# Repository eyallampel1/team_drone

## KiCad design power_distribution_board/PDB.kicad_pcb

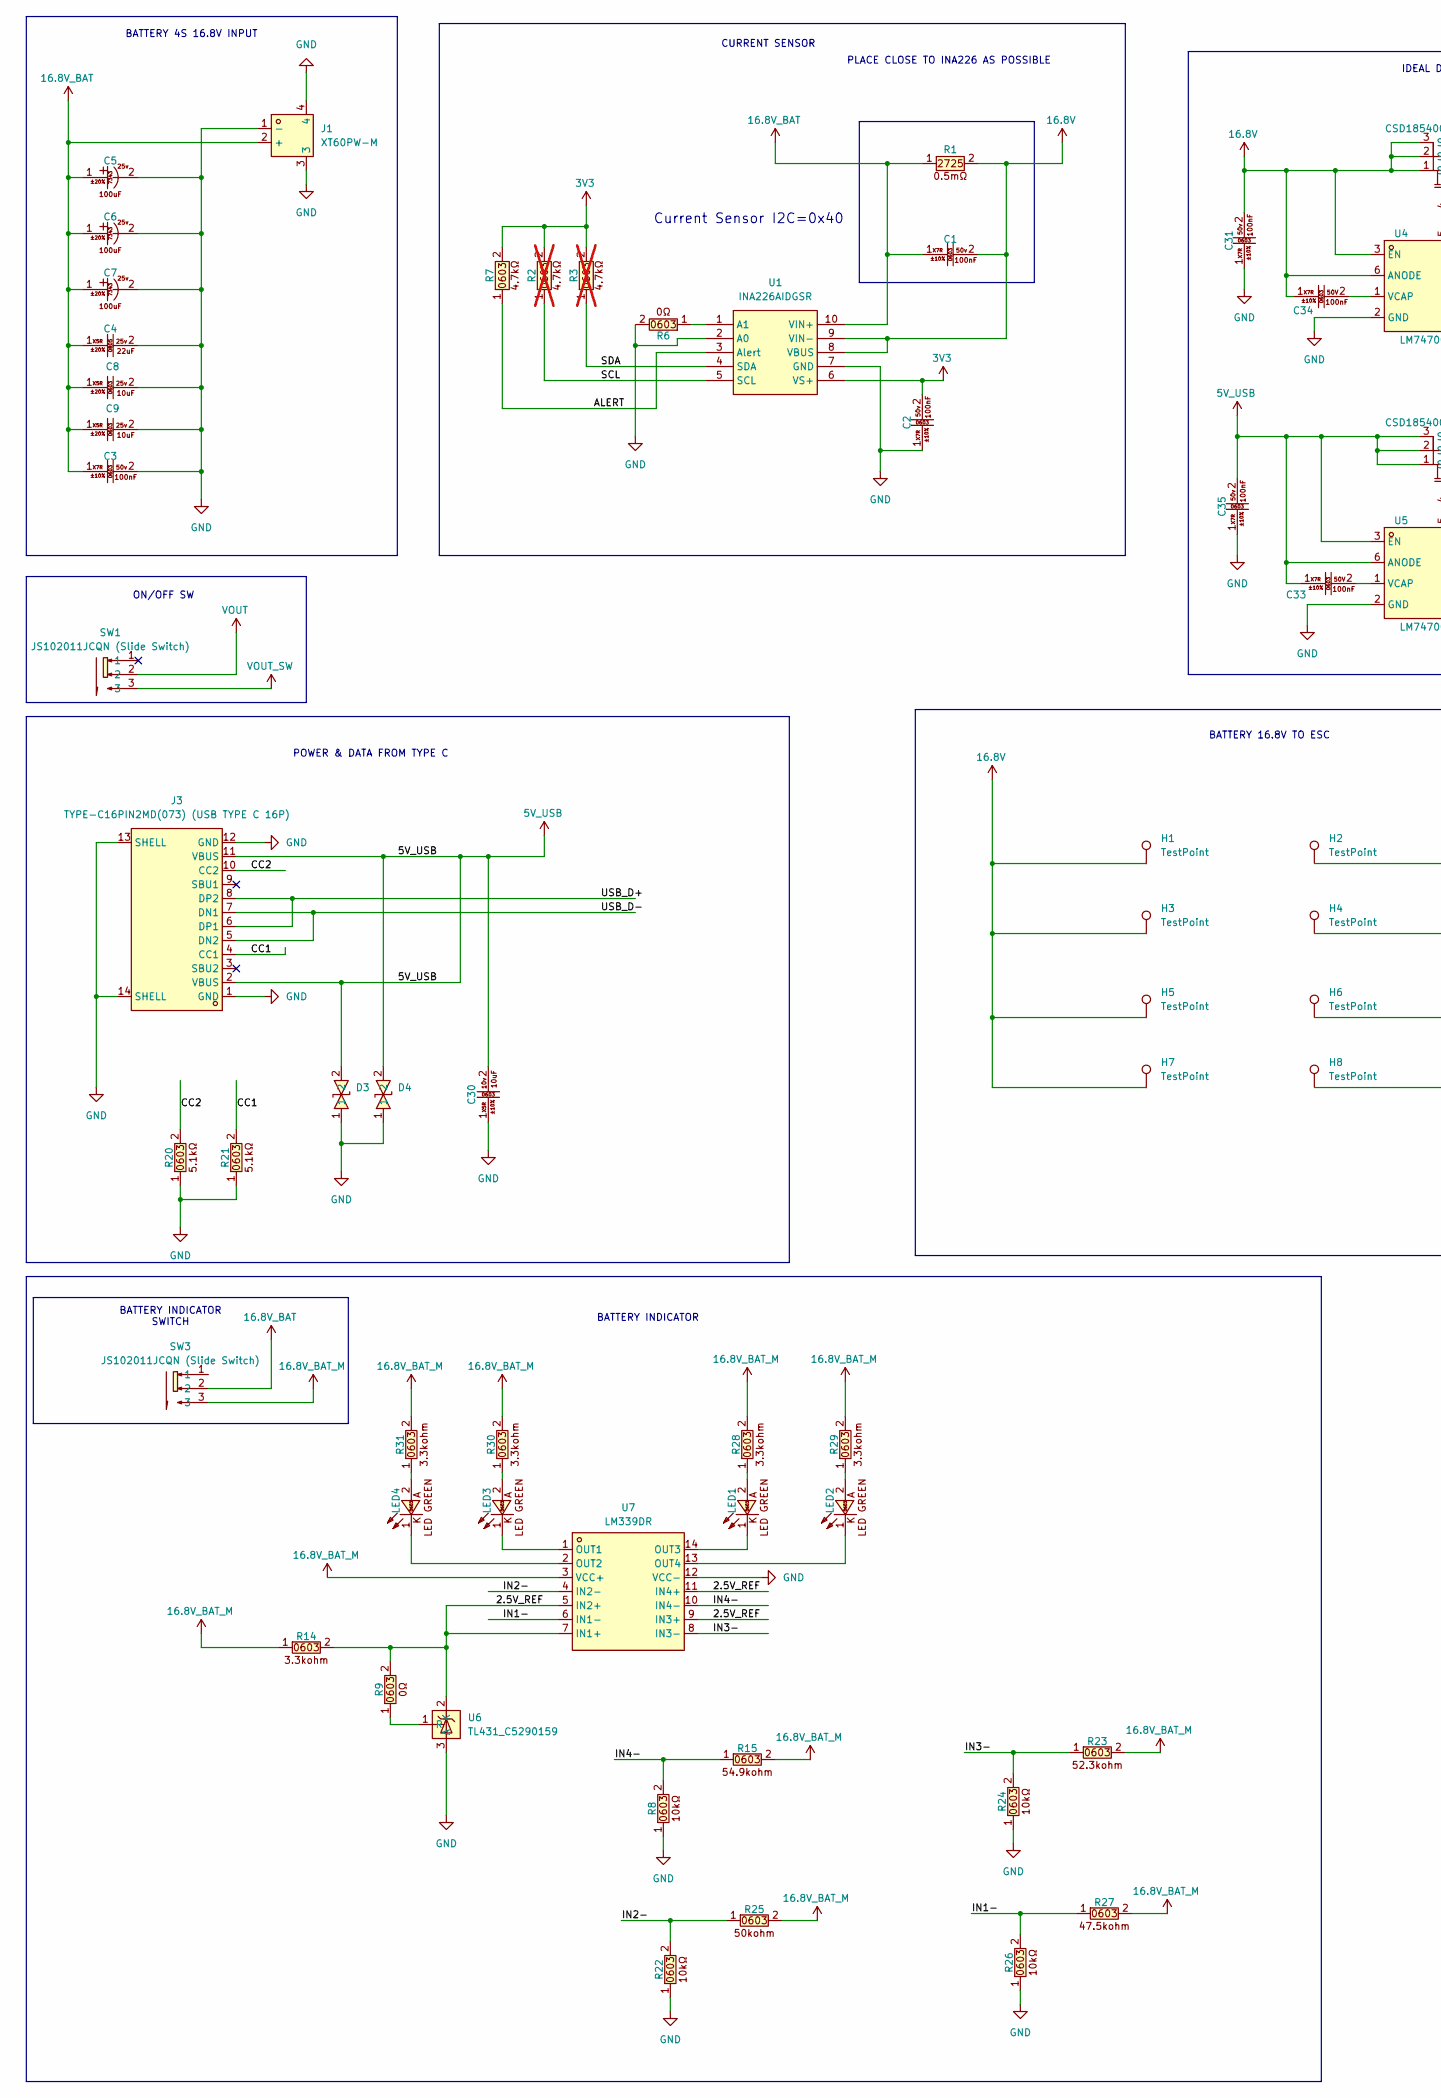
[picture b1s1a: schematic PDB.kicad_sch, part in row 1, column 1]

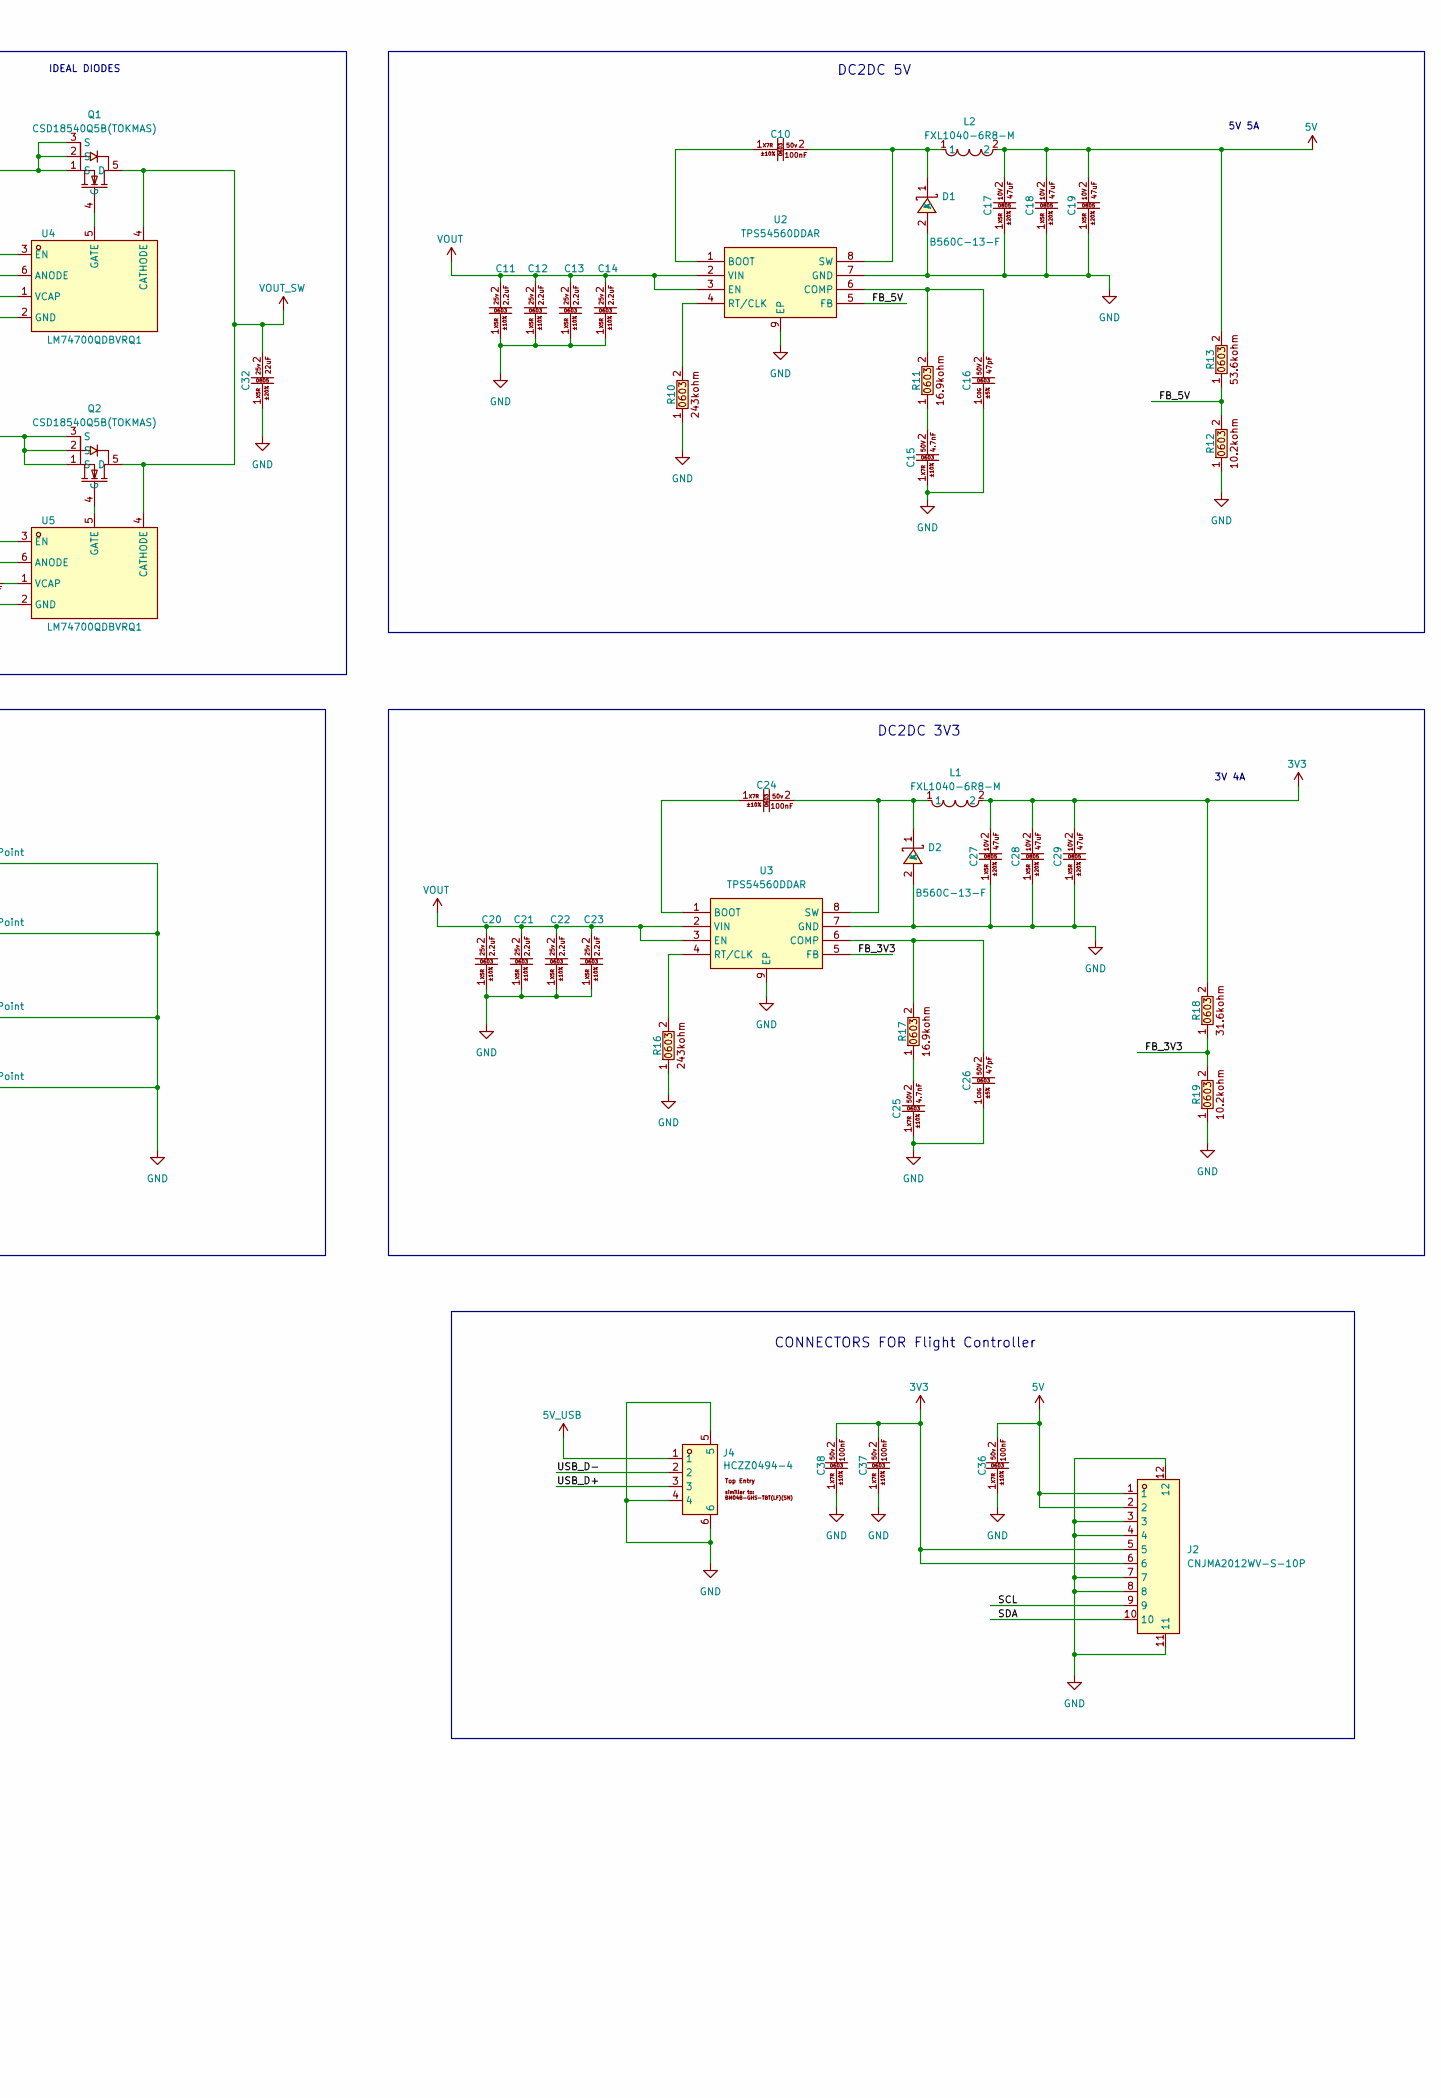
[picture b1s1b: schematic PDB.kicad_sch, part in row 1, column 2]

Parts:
C1, C2, C3, C10, C24, C31, C35, C36, C37, C38: CC0603KRX7R9BB104 (100nf , 0603 ,50v ,X7R); C0603; LCSC Part C14663
C4, C32: CL21A226MAYNNNE (22uf , 0805 ,25v ,X5R); C0805; LCSC Part C602037
C5, C6, C7: T521D107M025ATE040 (100uf , 7343 , 25v , tantalom); CAP-SMD_L7.3-W4.3_H2.8; LCSC Part C696814
C8, C9: CL10A106MA8NRNC (10uf , 0603 ,25v ,X5R); C0603; LCSC Part C96446
C11, C12, C13, C14, C20, C21, C22, C23: CL10A225KA8NNNC; C0603; LCSC Part C57895
C15, C25: CL10B472KB8NNNC (4.7nF , 0603 ,50V ,X7R); C0603; LCSC Part C1621
C16, C26: CL10C470JB8NNNC (47pF , 0603 ,50V ,C0G); C0603; LCSC Part C1671
C17, C18, C19, C27, C28, C29: GRM21BR61A476ME15L (47uF , 0805 ,10V ,X5R); C0805; LCSC Part C124129
C30: CL10A106KP8NNNC (10uf , 0603 ,10v,X5R); C0603; LCSC Part C19702
C33, C34: CC0603KRX7R9BB104 (100nF , 0603 ,50V ,X7R); C0603; LCSC Part C14663
D1, D2: B560C-13-F; SMC_L7.1-W6.2-LS8.1-RD; LCSC Part C85100
D3, D4: 603ESDA-05N (usb , esd , 0603); D0603-BI; LCSC Part C316054
H1, H2, H3, H4, H5, H6, H7, H8: TestPoint; TestPoint_THTPad_4.0x4.0mm_Drill2.0mm
J1: XT60PW-M; CONN-TH_XT60PW-M; LCSC Part C98732
J2: CNJMA2012WV-S-10P; CONN-SMD_10P-P2.00_CNJM_CNJMA2012WV-S-10P; LCSC Part C5151225
J3: TYPE-C16PIN2MD(073) (USB TYPE C 16P); USB-C-SMD_TYPE-C-6PIN-2MD-073; LCSC Part C2765186
J4: HCZZ0494-4; CONN-SMD_4P-P1.25_BM04B-GHS-TBT-LF-SN; LCSC Part C7433500
L1, L2: FXL1040-6R8-M; IND-SMD_L11.5-W10.0_FXL1040; LCSC Part C167231
LED1, LED2, LED3, LED4: 603Green509-620mcd (led green 0603); LED0603-RD; LCSC Part C12624
Q1, Q2: CSD18540Q5B(TOKMAS); TDSON-8_L5.9-W5.2-P1.27-BL; LCSC Part C19626234
R1: HOLR2725D-4W-0.5MR-1% ( 0.5mohm , 2725); R2725; LCSC Part C500744
R2, R3: FRC0603F4701TS (4.7kohm , 0603); R0603; LCSC Part C2907034; not fitted
R6, R9: 603WAF0000T5E (0ohm , 0603); R0603; LCSC Part C21189
R7: FRC0603F4701TS (4.7kohm , 0603); R0603; LCSC Part C2907034
R8, R22, R24, R26: 603WAF1002T5E (10kohm , 0603); R0603; LCSC Part C25804
R10, R16: 0603WAF2433T5E (243kohm , 0603); R0603; LCSC Part C23351
R11, R17: 0603WAF1692T5E (16.9kohm , 0603); R0603; LCSC Part C25954
R12, R19: 0603WAF1022T5E (10.2kohm , 0603); R0603; LCSC Part C22772
R13: 0603WAF5362T5E (53.6kohm , 0603); R0603; LCSC Part C23074
R14, R28, R29, R30, R31: 0603WAF3301T5E (3.3kohm , 0603); R0603; LCSC Part C22978
R15: 0603WAF5492T5E (54.9kohm , 0603); R0603; LCSC Part C23077
R18: 0603WAF3162T5E (31.6kohm , 0603); R0603; LCSC Part C25967
R20, R21: 603WAF5101T5E (5.1kohm , 0603); R0603; LCSC Part C23186
R23: 0603WAF5232T5E (52.3kohm , 0603); R0603; LCSC Part C23198
R25: RT0603BRD0750KL (50kohm , 0603); R0603; LCSC Part C861451
R27: 0603WAF4752T5E (47.5kohm , 0603); R0603; LCSC Part C23061
SW1, SW3: JS102011JCQN (Slide Switch); SW-SMD_JS102011JCQN; LCSC Part C221659
U1: INA226AIDGSR; MSOP-10_L3.0-W3.0-P0.50-LS5.0-BL; LCSC Part C49851
U2, U3: TPS54560DDAR; SOIC-8_L5.0-W4.0-P1.27-LS6.0-BL-EP2.0; LCSC Part C31966
U4, U5: LM74700QDBVRQ1; SOT-23-6_L2.9-W1.6-P0.95-LS2.8-BL; LCSC Part C2941042
U6: TL431_C5290159; SOT-23-3_L2.9-W1.4-P1.90-LS2.6-BR; LCSC Part C5290159
U7: LM339DR; SOIC-14_L8.7-W3.9-P1.27-LS6.0-BL; LCSC Part C7948

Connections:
3V3: C2.2, C27.2, C28.2, C29.2, C37.2, C38.2, J2.5, J2.6, L1.2, R2.2, R3.2, R7.2, R18.2, U1.6 (VS+)
5V: C17.2, C18.2, C19.2, C36.2, J2.1, J2.2, L2.2, R13.2
5V_USB: C30.2, C33.1, C35.2, D3.2, D4.2, J3.2 (VBUS), J3.11 (VBUS), J4.1, Q2.1 (S), Q2.2 (S), Q2.3 (S), U5.3 (EN), U5.6 (ANODE)
16.8V: C1.2, C31.2, C34.1, H1.1, H3.1, H5.1, H7.1, Q1.1 (S), Q1.2 (S), Q1.3 (S), R1.2, U1.8 (VBUS), U1.9 (VIN-), U4.3 (EN), U4.6 (ANODE)
16.8V_BAT: C1.1, C3.1, C4.1, C5.1, C6.1, C7.1, C8.1, C9.1, J1.2 (+), R1.1, SW3.2, U1.10 (VIN+)
16.8V_BAT_M: R14.1, R15.2, R23.2, R25.2, R27.2, R28.2, R29.2, R30.2, R31.2, SW3.3, U7.3 (VCC+)
/2.5V_REF: R9.2, R14.2, U6.2 (K), U7.5 (IN2+), U7.7 (IN1+), U7.9 (IN3+), U7.11 (IN4+)
/ALERT: R7.1, U1.3 (Alert)
/CC1: J3.4 (CC1), R21.2
/CC2: J3.10 (CC2), R20.2
/FB_3V3: R18.1, R19.2, U3.5 (FB)
/FB_5V: R12.2, R13.1, U2.5 (FB)
/IN1-: R26.2, R27.1, U7.6 (IN1-)
/IN2-: R22.2, R25.1, U7.4 (IN2-)
/IN3-: R23.1, R24.2, U7.8 (IN3-)
/IN4-: R8.2, R15.1, U7.10 (IN4-)
/SCL: J2.9, R2.1, U1.5 (SCL)
/SDA: J2.10, R3.1, U1.4 (SDA)
/USB_D+: J3.6 (DP1), J3.8 (DP2), J4.3
/USB_D-: J3.5 (DN2), J3.7 (DN1), J4.2
GND: C2.1, C3.2, C4.2, C5.2, C6.2, C7.2, C8.2, C9.2, C11.1, C12.1, C13.1, C14.1, C15.1, C16.1, C17.1, C18.1, C19.1, C20.1, C21.1, C22.1, C23.1, C25.1, C26.1, C27.1, C28.1, C29.1, C30.1, C31.1, C32.1, C35.1, C36.1, C37.1, C38.1, D1.2 (A), D2.2 (A), D3.1, D4.1, H2.1, H4.1, H6.1, H8.1, J1.1 (-), J1.3, J1.4, J2.3, J2.4, J2.7, J2.8, J2.11, J2.12, J3.1 (GND), J3.12 (GND), J3.13 (SHELL), J3.14 (SHELL), J4.4, J4.5, J4.6, R6.2, R8.1, R10.1, R12.1, R16.1, R19.1, R20.1, R21.1, R22.1, R24.1, R26.1, U1.2 (A0), U1.7 (GND), U2.7 (GND), U2.9 (EP), U3.7 (GND), U3.9 (EP), U4.2 (GND), U5.2 (GND), U6.3 (A), U7.12 (VCC-)
unnamed: C15.2, R11.1
unnamed: C25.2, R17.1
unnamed: C10.2, D1.1 (K), L2.1, U2.8 (SW)
unnamed: C24.2, D2.1 (K), L1.1, U3.8 (SW)
unnamed: LED1.2, R28.1
unnamed: LED2.2, R29.1
unnamed: LED3.2, R30.1
unnamed: LED4.2, R31.1
unnamed: Q1.4 (G), U4.5 (GATE)
unnamed: Q2.4 (G), U5.5 (GATE)
unnamed: R6.1, U1.1 (A1)
unnamed: C10.1, U2.1 (BOOT)
unnamed: C16.2, R11.2, U2.6 (COMP)
unnamed: R10.2, U2.4 (RT/CLK)
unnamed: C24.1, U3.1 (BOOT)
unnamed: C26.2, R17.2, U3.6 (COMP)
unnamed: R16.2, U3.4 (RT/CLK)
unnamed: C34.2, U4.1 (VCAP)
unnamed: C33.2, U5.1 (VCAP)
unnamed: R9.1, U6.1 (R)
unnamed: LED3.1, U7.1 (OUT1)
unnamed: LED4.1, U7.2 (OUT2)
unnamed: LED1.1, U7.14 (OUT3)
unnamed: LED2.1, U7.13 (OUT4)
VOUT: C11.2, C12.2, C13.2, C14.2, C20.2, C21.2, C22.2, C23.2, SW1.2, U2.2 (VIN), U2.3 (EN), U3.2 (VIN), U3.3 (EN)
VOUT_SW: C32.2, Q1.5 (D), Q2.5 (D), SW1.3, U4.4 (CATHODE), U5.4 (CATHODE)

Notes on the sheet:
Current Sensor I2C=0x40
CONNECTORS FOR Flight Controller
DC2DC 5V
PLACE CLOSE TO INA226 AS POSSIBLE
POWER & DATA FROM TYPE C
5V 5A
BATTERY 4S 16.8V INPUT
BATTERY INDICATOR
DC2DC 3V3
CURRENT SENSOR
BATTERY INDICATOR SWITCH
IDEAL DIODES
ON/OFF SW
BATTERY 16.8V TO ESC
3V 4A

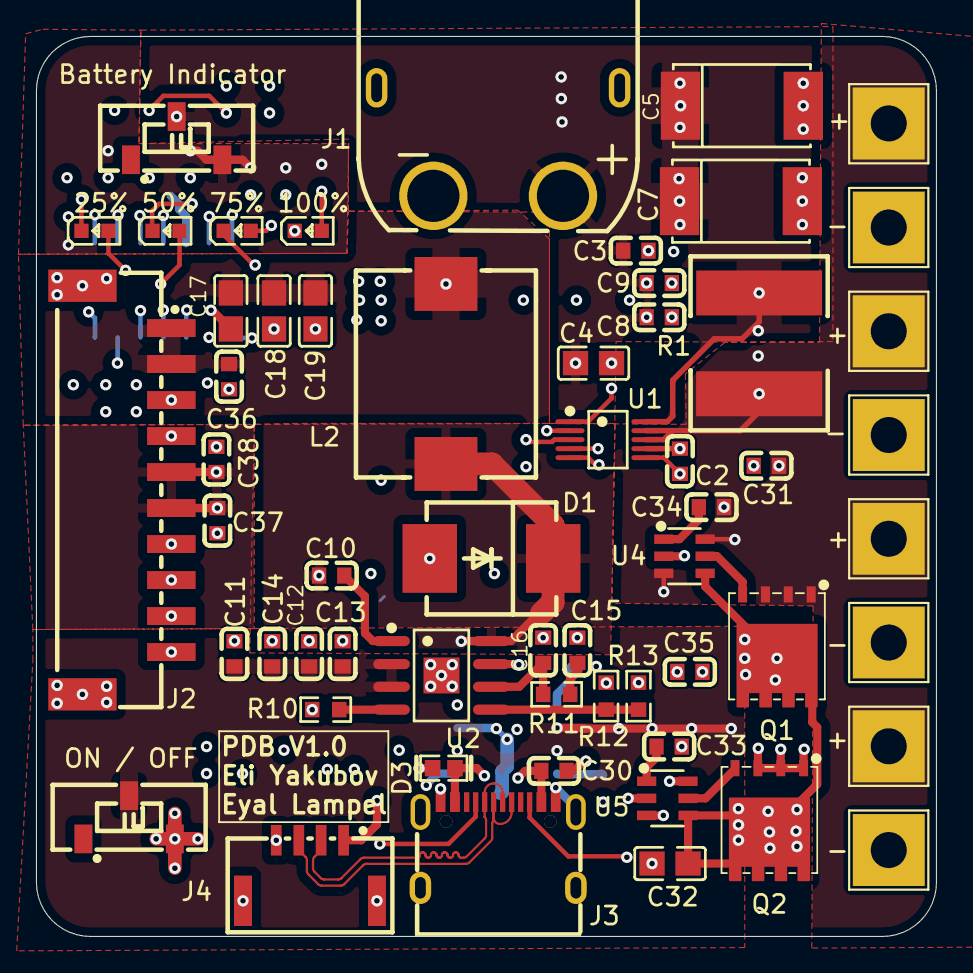
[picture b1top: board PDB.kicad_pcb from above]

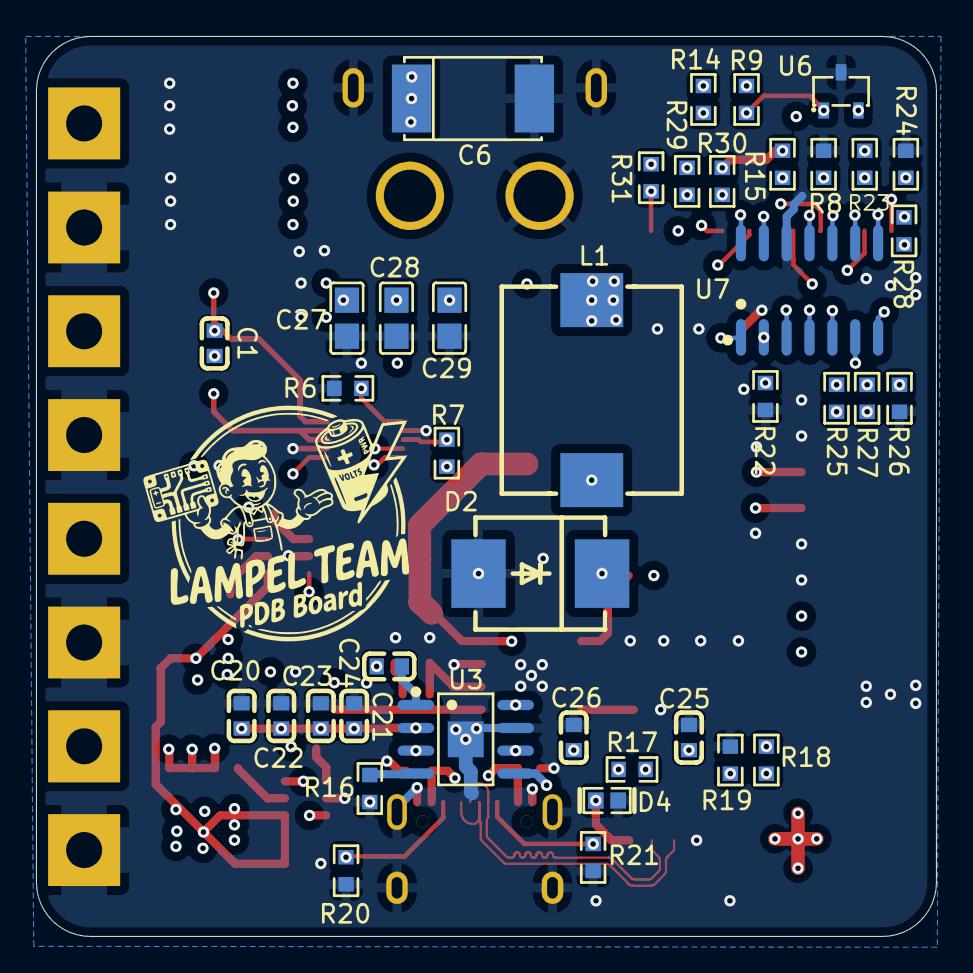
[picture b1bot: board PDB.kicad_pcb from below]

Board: 6 copper layers, 50.0 x 50.0 mm, 98 parts (40 on the bottom side), 47 nets.

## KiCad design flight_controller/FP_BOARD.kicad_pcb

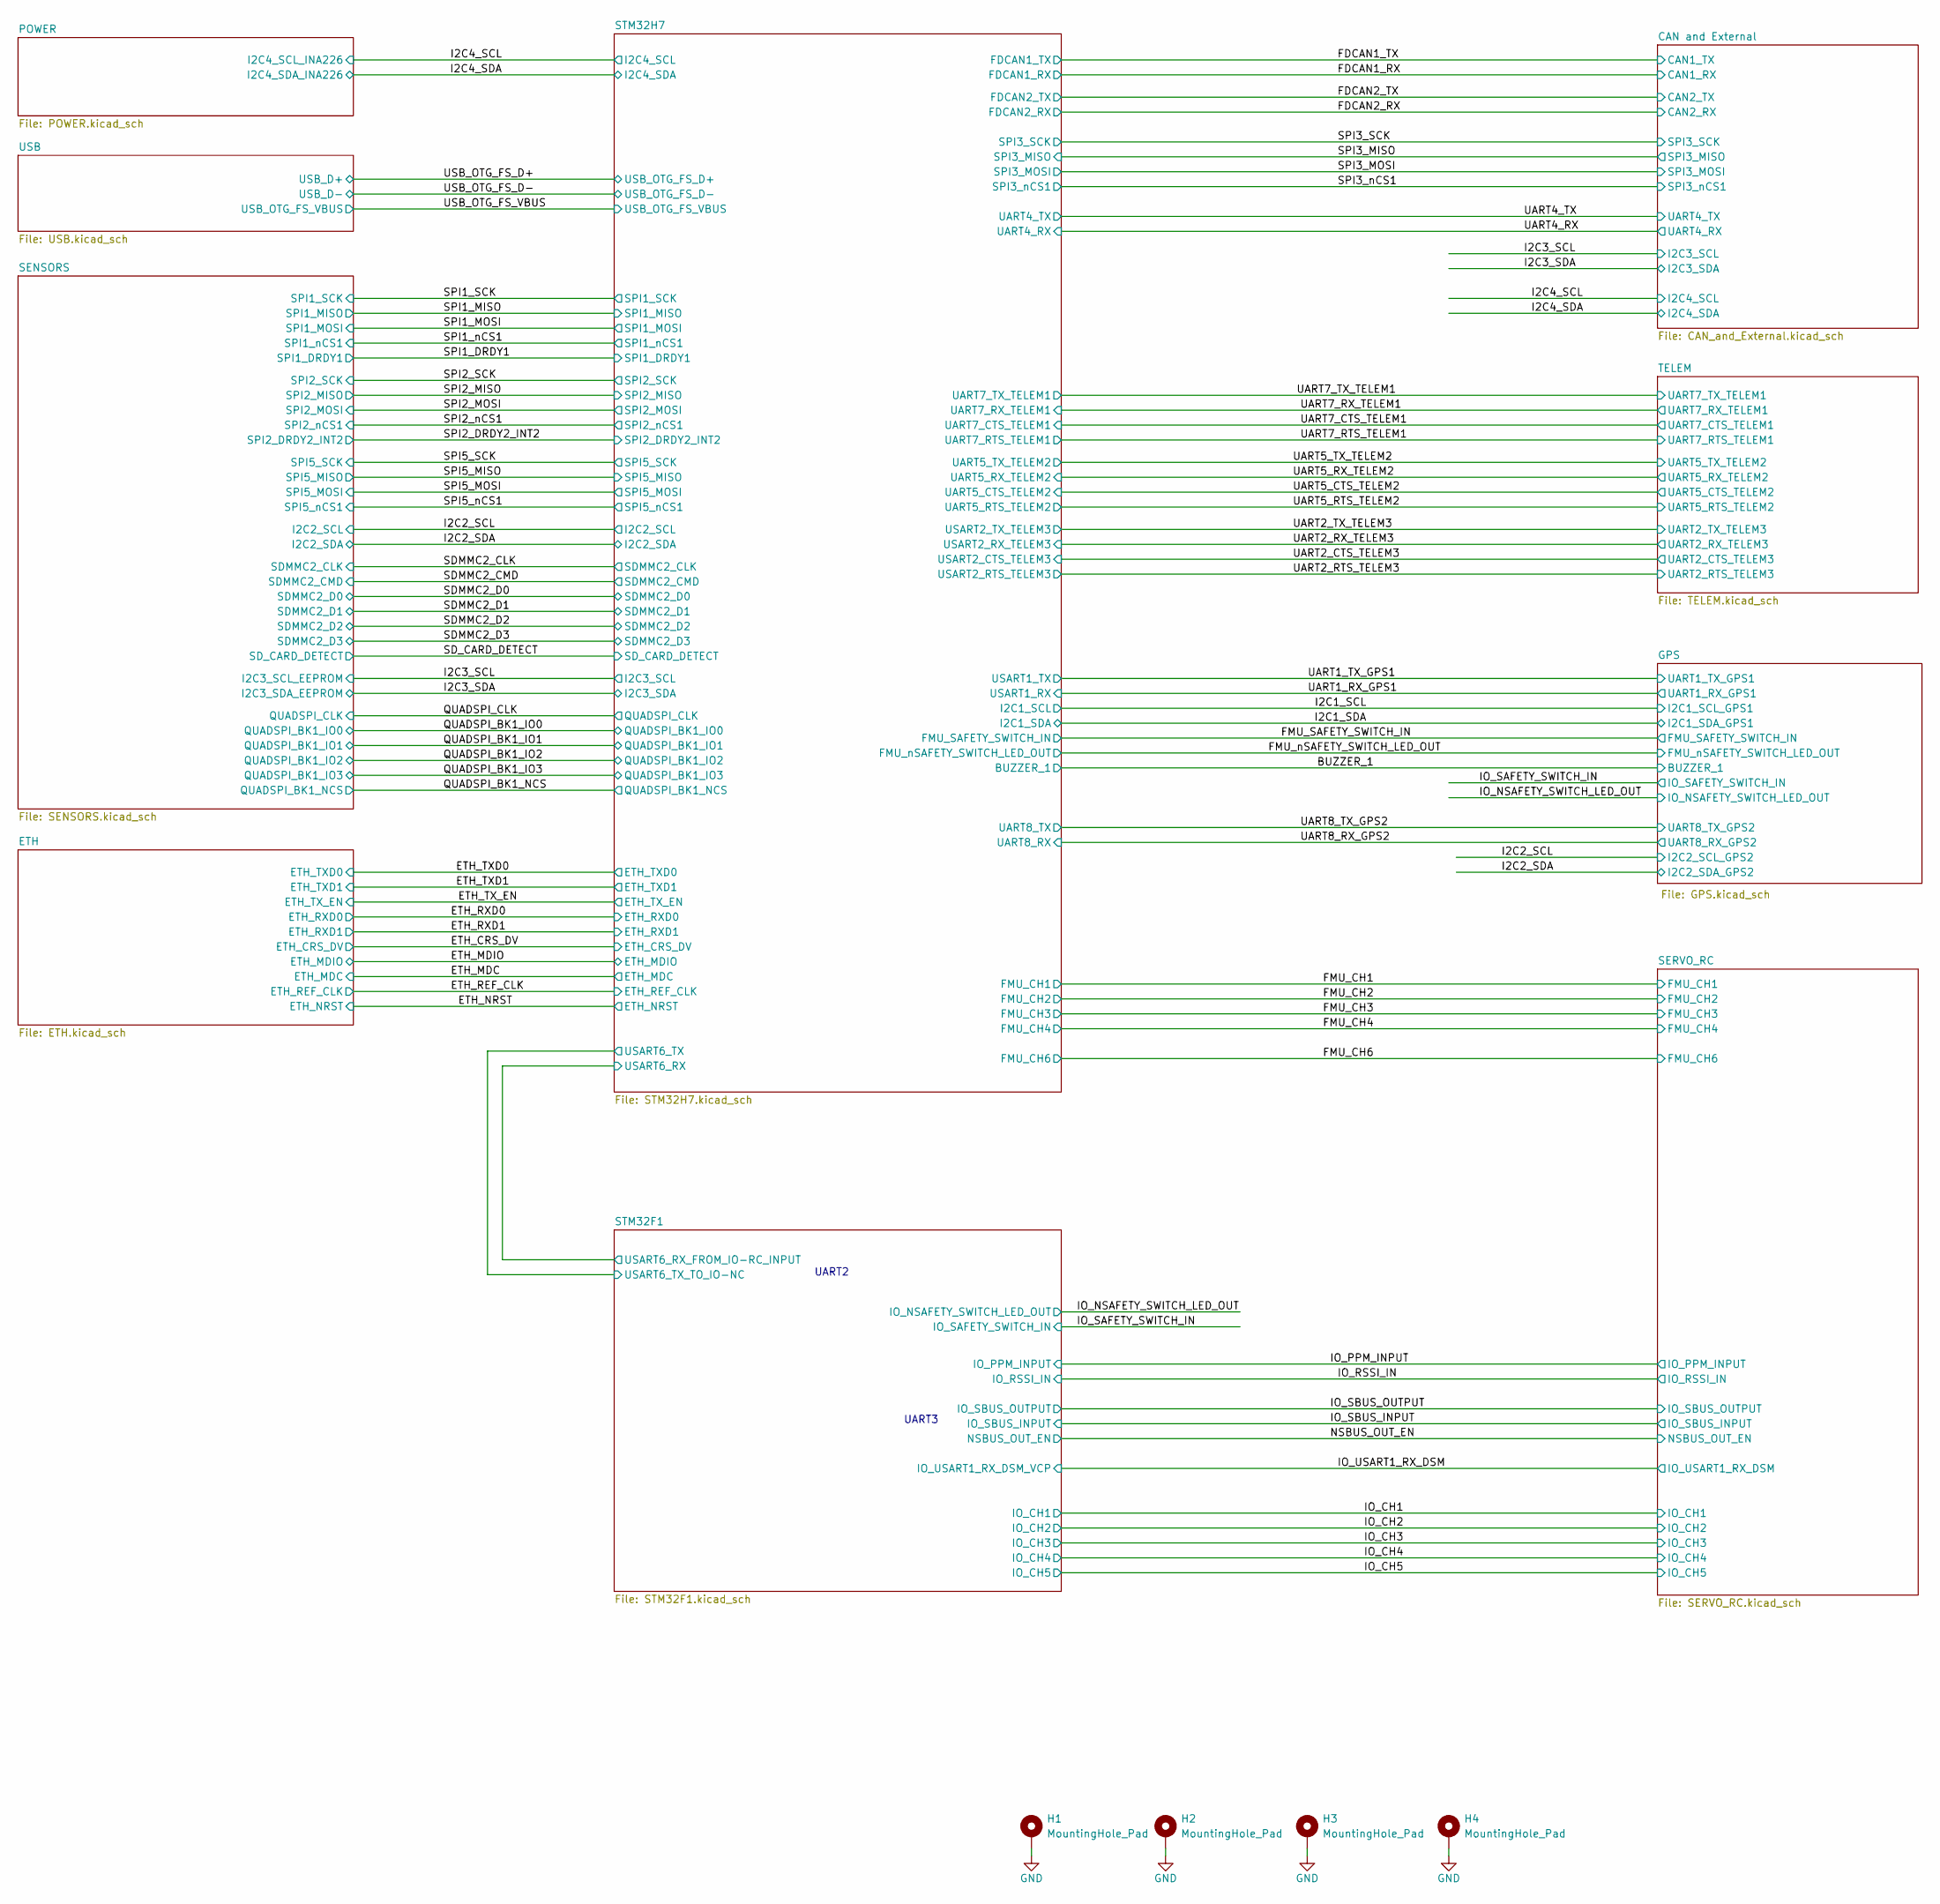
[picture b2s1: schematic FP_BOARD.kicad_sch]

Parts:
H1, H2, H3, H4: MountingHole_Pad; MountingHole_2.2mm_M2_Pad

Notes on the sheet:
UART2
UART3

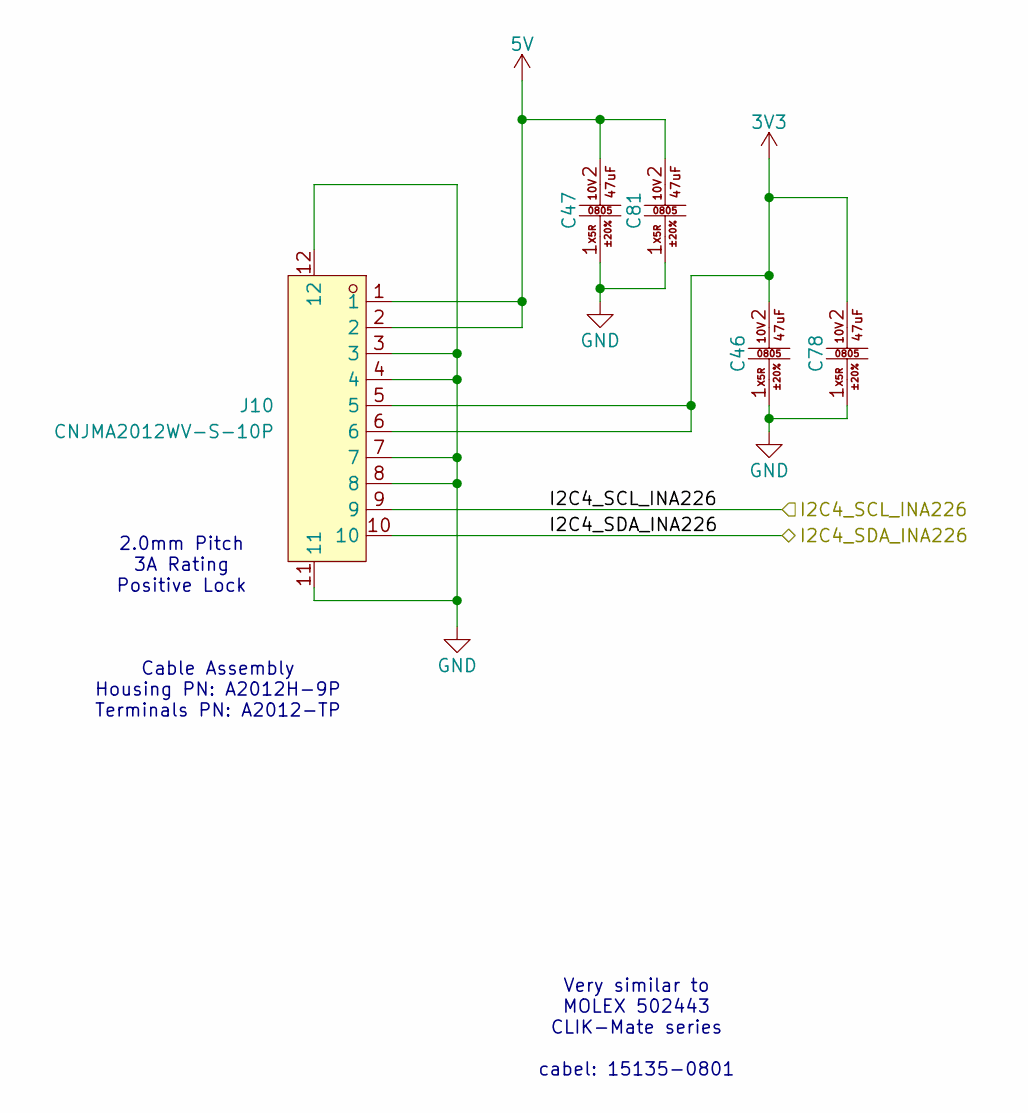
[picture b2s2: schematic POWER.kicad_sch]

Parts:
C46, C47, C78, C81: GRM21BR61A476ME15L (47uF , 0805 ,10V ,X5R); C0805; LCSC Part C124129
J10: CNJMA2012WV-S-10P; CONN-SMD_10P-P2.00_CNJM_CNJMA2012WV-S-10P; LCSC Part C5151225

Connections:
/I2C4_SCL: J10.9; also elsewhere on the board
/I2C4_SDA: J10.10; also elsewhere on the board

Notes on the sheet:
Cable Assembly Housing PN: A2012H-9P Terminals PN: A2012-TP
Very similar to MOLEX 502443 CLIK-Mate series cabel: 15135-0801
2.0mm Pitch 3A Rating Positive Lock

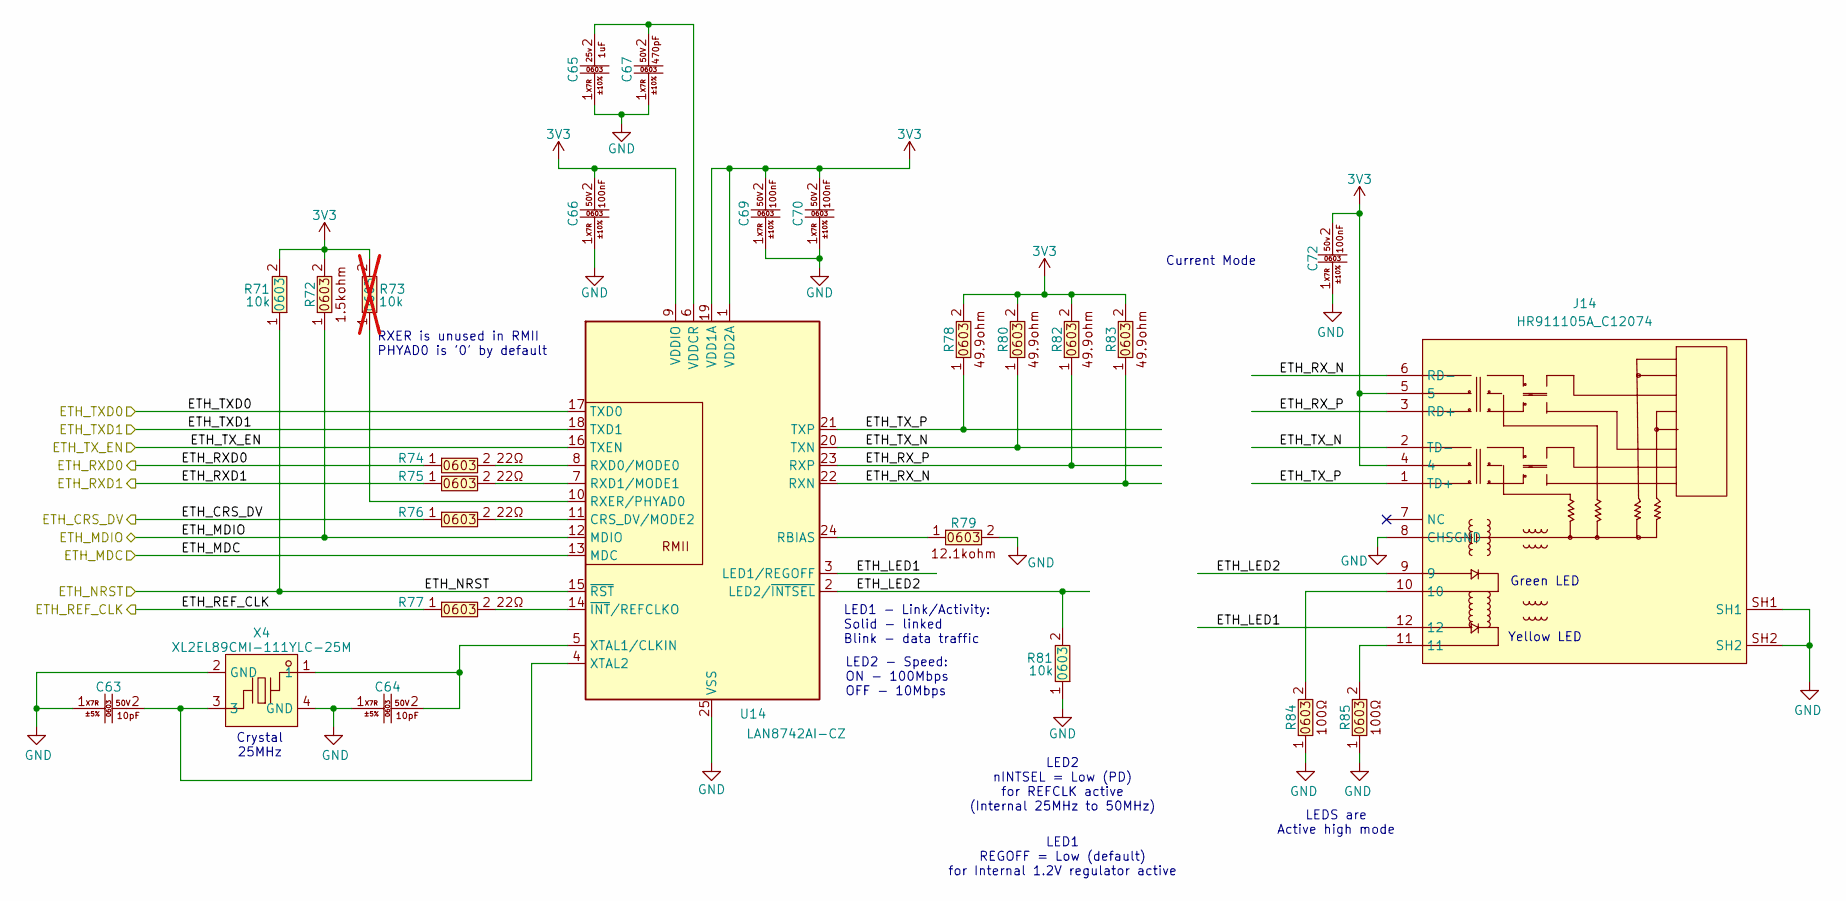
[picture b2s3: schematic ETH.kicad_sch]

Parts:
C63, C64: CC0603JRNPO9BN100 (10pF , 0603 ,50V ,X7R); C0603; LCSC Part C106245
C65: CL10B105KA8NNNC (1uf ,0603 ,25v ,X7R); C0603; LCSC Part C29936
C66, C69, C70: CC0603KRX7R9BB104 (100nF , 0603 ,50V ,X7R); C0603; LCSC Part C14663
C67: CC0603KRX7R9BB471 (470pF , 0603 ,50V ,X7R); C0603; LCSC Part C107092
C72: CC0603KRX7R9BB104 (100nf , 0603 ,50v ,X7R); C0603; LCSC Part C14663
J14: HR911105A_C12074; RJ45-TH_HR911105A; LCSC Part C12074
R71, R81: 0603WAF1002T5E; R0603; LCSC Part C25804
R72: 0603WAF1501T5E (1.5kohm , 0603); R0603; LCSC Part C22843
R73: 0603WAF1002T5E; R0603; LCSC Part C25804; not fitted
R74, R75, R76, R77: 603WAF220JT5E (22ohm , 0603); R0603; LCSC Part C23345
R78, R80, R82, R83: 0603WAF499JT5E (49.9ohm , 0603); R0603; LCSC Part C23185
R79: 0603WAF1212T5E (12.1kohm , 0603); R0603; LCSC Part C22864
R84, R85: 603WAF1000T5E (100ohm , 0603); R0603; LCSC Part C22775
U14: LAN8742AI-CZ; QFN-24_L4.0-W4.0-P0.50-BL-EP2.6; LCSC Part C153279
X4: XL2EL89CMI-111YLC-25M; CRYSTAL-SMD_4P-L3.2-W2.5-BL_SIT8008BI; LCSC Part C5444611

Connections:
/ETH/ETH_LED1: J14.12, U14.3 (LED1/REGOFF)
/ETH/ETH_LED2: J14.9, R81.2, U14.2 (LED2/~INTSEL)
/ETH_CRS_DV: R76.1; also elsewhere on the board
/ETH_MDC: U14.13 (MDC); also elsewhere on the board
/ETH_MDIO: R72.1, U14.12 (MDIO); also elsewhere on the board
/ETH_NRST: R71.1, U14.15 (~RST); also elsewhere on the board
/ETH_REF_CLK: R77.1; also elsewhere on the board
/ETH_RXD0: R74.1; also elsewhere on the board
/ETH_RXD1: R75.1; also elsewhere on the board
/ETH_TXD0: U14.17 (TXD0); also elsewhere on the board
/ETH_TXD1: U14.18 (TXD1); also elsewhere on the board
/ETH_TX_EN: U14.16 (TXEN); also elsewhere on the board
unnamed: J14.10, R84.2
unnamed: J14.11, R85.2
unnamed: R76.2, U14.11 (CRS_DV/MODE2)
unnamed: R79.1, U14.24 (RBIAS)
unnamed: R74.2, U14.8 (RXD0/MODE0)
unnamed: R75.2, U14.7 (RXD1/MODE1)
unnamed: R73.1, U14.10 (RXER/PHYAD0)
unnamed: C65.2, C67.2, U14.6 (VDDCR)
unnamed: C64.2, U14.5 (XTAL1/CLKIN), X4.1
unnamed: C63.2, U14.4 (XTAL2), X4.3
unnamed: R77.2, U14.14 (~INT/REFCLKO)

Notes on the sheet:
LED2 - Speed: ON - 100Mbps OFF - 10Mbps
Yellow LED
RXER is unused in RMII PHYAD0 is '0' by default
Green LED
Crystal 25MHz
LEDS are Active high mode
LED1 - Link/Activity: Solid - linked Blink - data traffic
Current Mode
LED2 nINTSEL = Low (PD) for REFCLK active (Internal 25MHz to 50MHz)
LED1 REGOFF = Low (default) for Internal 1.2V regulator active
